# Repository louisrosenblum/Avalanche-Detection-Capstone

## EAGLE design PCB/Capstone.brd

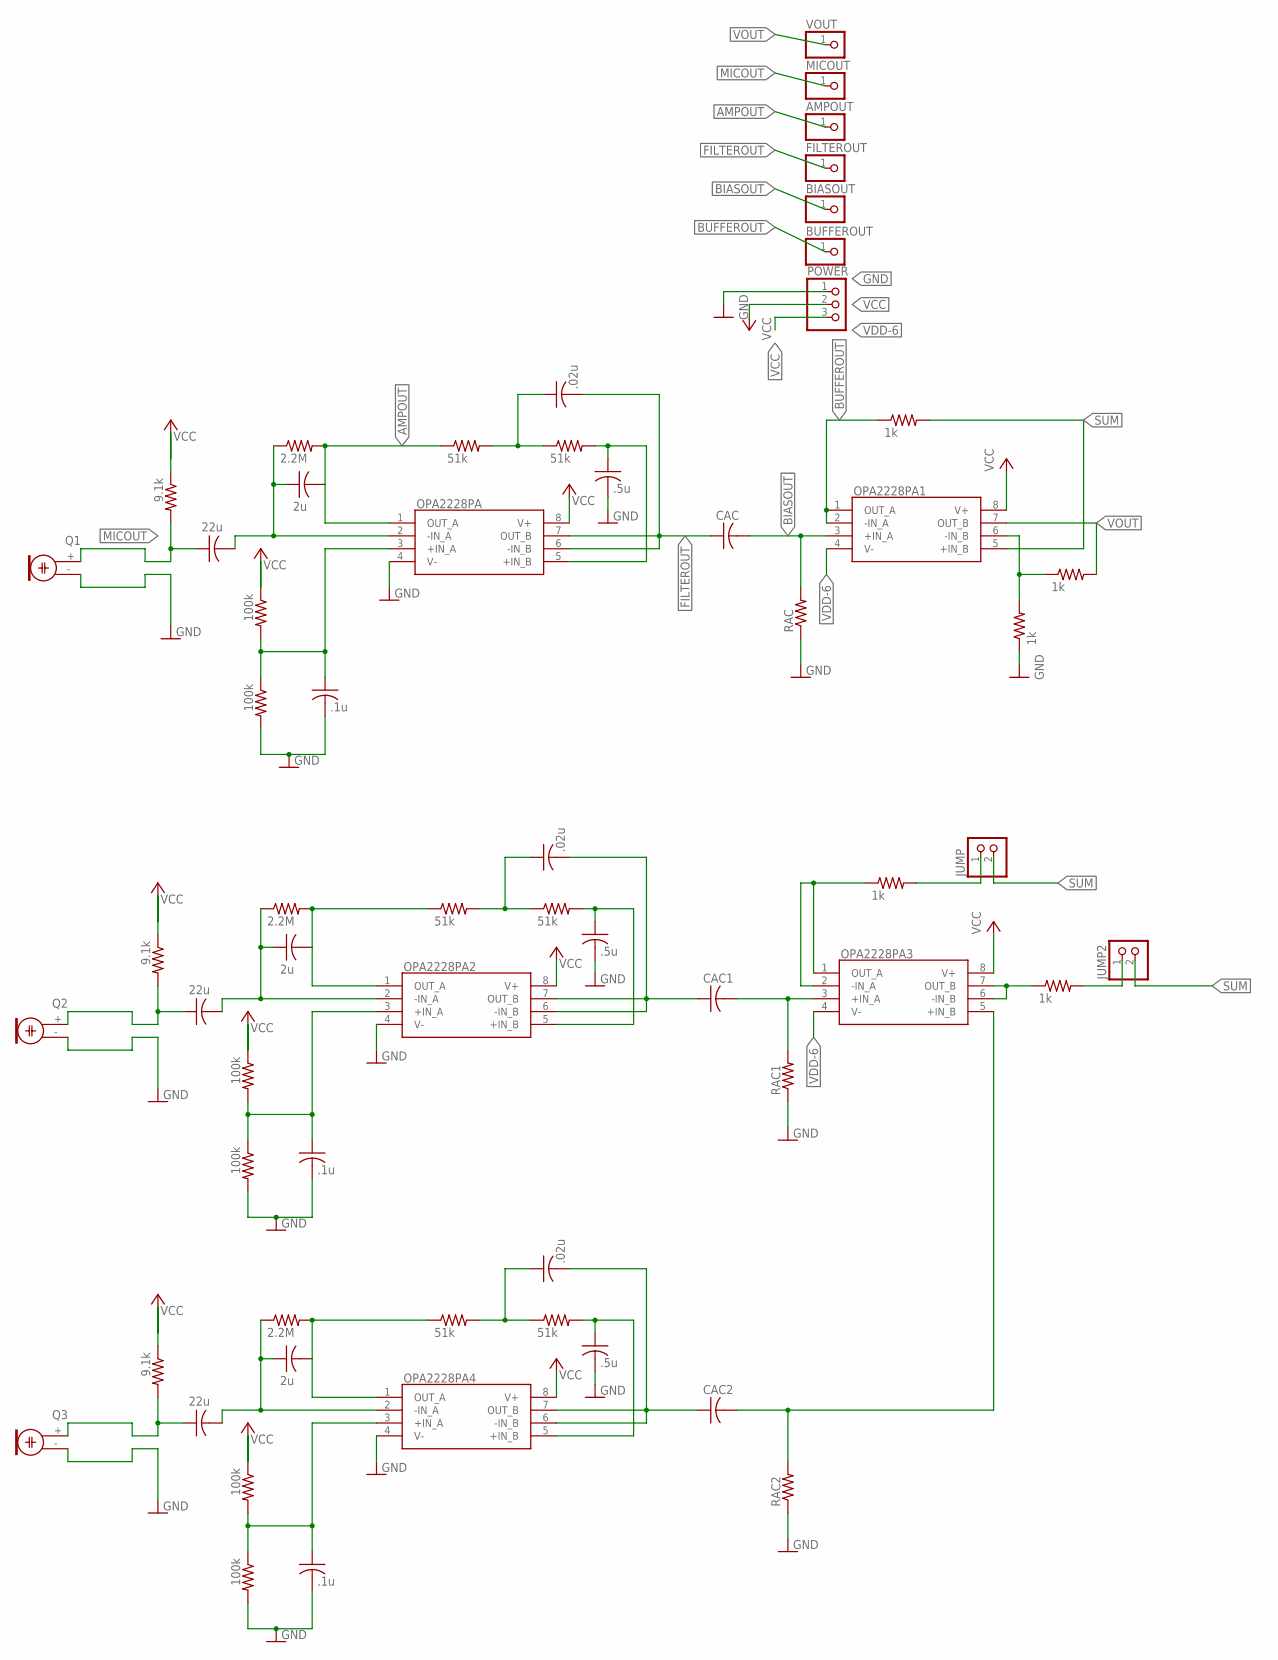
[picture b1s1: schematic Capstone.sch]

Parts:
AMPOUT: PINHD-1X1; 1X01
BIASOUT: PINHD-1X1; 1X01
BUFFEROUT: PINHD-1X1; 1X01
C1, C6, C11: .1u; C025-024X044
C2, C7, C12: 2u; C025-024X044
C3, C8, C13: 22u; C025-024X044
C4, C9, C14: .02u; C025-024X044
C5, C10, C15: .5u; C025-024X044
CAC, CAC1, CAC2: C-US025-024X044; C025-024X044
FILTEROUT: PINHD-1X1; 1X01
JUMP, JUMP2: PINHD-1X2; 1X02
MICOUT: PINHD-1X1; 1X01
OPA2228PA, OPA2228PA1, OPA2228PA2, OPA2228PA3, OPA2228PA4: OPA2228PA; DIP794W53P254L959H508Q8N
POWER: PINHD-1X3; 1X03
Q1, Q2, Q3: ELECTRET; 9.7ELECTRET
R1, R10, R17: 9.1k; 0204/7
R2, R3, R11, R12, R18, R19: 100k; 0204/7
R4, R13, R20: 2.2M; 0204/7
R5, R6, R14, R15, R21, R22: 51k; 0204/7
R7, R8, R9, R16, R23: 1k; 0204/7
RAC, RAC1, RAC2: R-US_0204/7; 0204/7
VOUT: PINHD-1X1; 1X01

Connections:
1: C8.1, Q2.+ (2), R10.2
2: C13.1, Q3.+ (2), R17.2
AMPOUT: AMPOUT.1, C2.2, OPA2228PA.1 (OUT_A), R4.2, R5.1
AMPOUT1: C7.2, OPA2228PA2.1 (OUT_A), R13.2, R14.1
AMPOUT2: C12.2, OPA2228PA4.1 (OUT_A), R20.2, R21.1
BIASOUT: BIASOUT.1, CAC.2, OPA2228PA1.3 (+IN_A), RAC.2
BIASOUT1: CAC1.2, OPA2228PA3.3 (+IN_A), RAC1.2
BIASOUT2: CAC2.2, OPA2228PA3.5 (+IN_B), RAC2.2
BUFFEROUT: BUFFEROUT.1, OPA2228PA1.1 (OUT_A), OPA2228PA1.2 (-IN_A), R8.1
FILTEROUT: C4.2, CAC.1, FILTEROUT.1, OPA2228PA.6 (-IN_B), OPA2228PA.7 (OUT_B)
FILTEROUT1: C9.2, CAC1.1, OPA2228PA2.6 (-IN_B), OPA2228PA2.7 (OUT_B)
FILTEROUT2: C14.2, CAC2.1, OPA2228PA4.6 (-IN_B), OPA2228PA4.7 (OUT_B)
GND: C1.2, C5.2, C6.2, C10.2, C11.2, C15.2, OPA2228PA.4 (V-), OPA2228PA2.4 (V-), OPA2228PA4.4 (V-), POWER.1, Q1.- (1), Q2.- (1), Q3.- (1), R3.2, R7.1, R12.2, R19.2, RAC.1, RAC1.1, RAC2.1
MICOUT: C3.1, MICOUT.1, Q1.+ (2), R1.2
unnamed: C6.1, OPA2228PA2.3 (+IN_A), R11.2, R12.1
unnamed: C2.1, C3.2, OPA2228PA.2 (-IN_A), R4.1
unnamed: OPA2228PA1.6 (-IN_B), R7.2, R9.1
unnamed: C1.1, OPA2228PA.3 (+IN_A), R2.2, R3.1
unnamed: C7.1, C8.2, OPA2228PA2.2 (-IN_A), R13.1
unnamed: C4.1, R5.2, R6.1
unnamed: C5.1, OPA2228PA.5 (+IN_B), R6.2
unnamed: C9.1, R14.2, R15.1
unnamed: JUMP.1, R16.2
unnamed: C10.1, OPA2228PA2.5 (+IN_B), R15.2
unnamed: OPA2228PA3.1 (OUT_A), OPA2228PA3.2 (-IN_A), R16.1
unnamed: C11.1, OPA2228PA4.3 (+IN_A), R18.2, R19.1
unnamed: C12.1, C13.2, OPA2228PA4.2 (-IN_A), R20.1
unnamed: C14.1, R21.2, R22.1
unnamed: C15.1, OPA2228PA4.5 (+IN_B), R22.2
unnamed: OPA2228PA3.6 (-IN_B), OPA2228PA3.7 (OUT_B), R23.1
unnamed: JUMP2.1, R23.2
SUM: JUMP.2, JUMP2.2, OPA2228PA1.5 (+IN_B), R8.2
VCC: OPA2228PA.8 (V+), OPA2228PA1.8 (V+), OPA2228PA2.8 (V+), OPA2228PA3.8 (V+), OPA2228PA4.8 (V+), POWER.2, R1.1, R2.1, R10.1, R11.1, R17.1, R18.1
VDD-6: OPA2228PA1.4 (V-), OPA2228PA3.4 (V-), POWER.3
VOUT: OPA2228PA1.7 (OUT_B), R9.2, VOUT.1

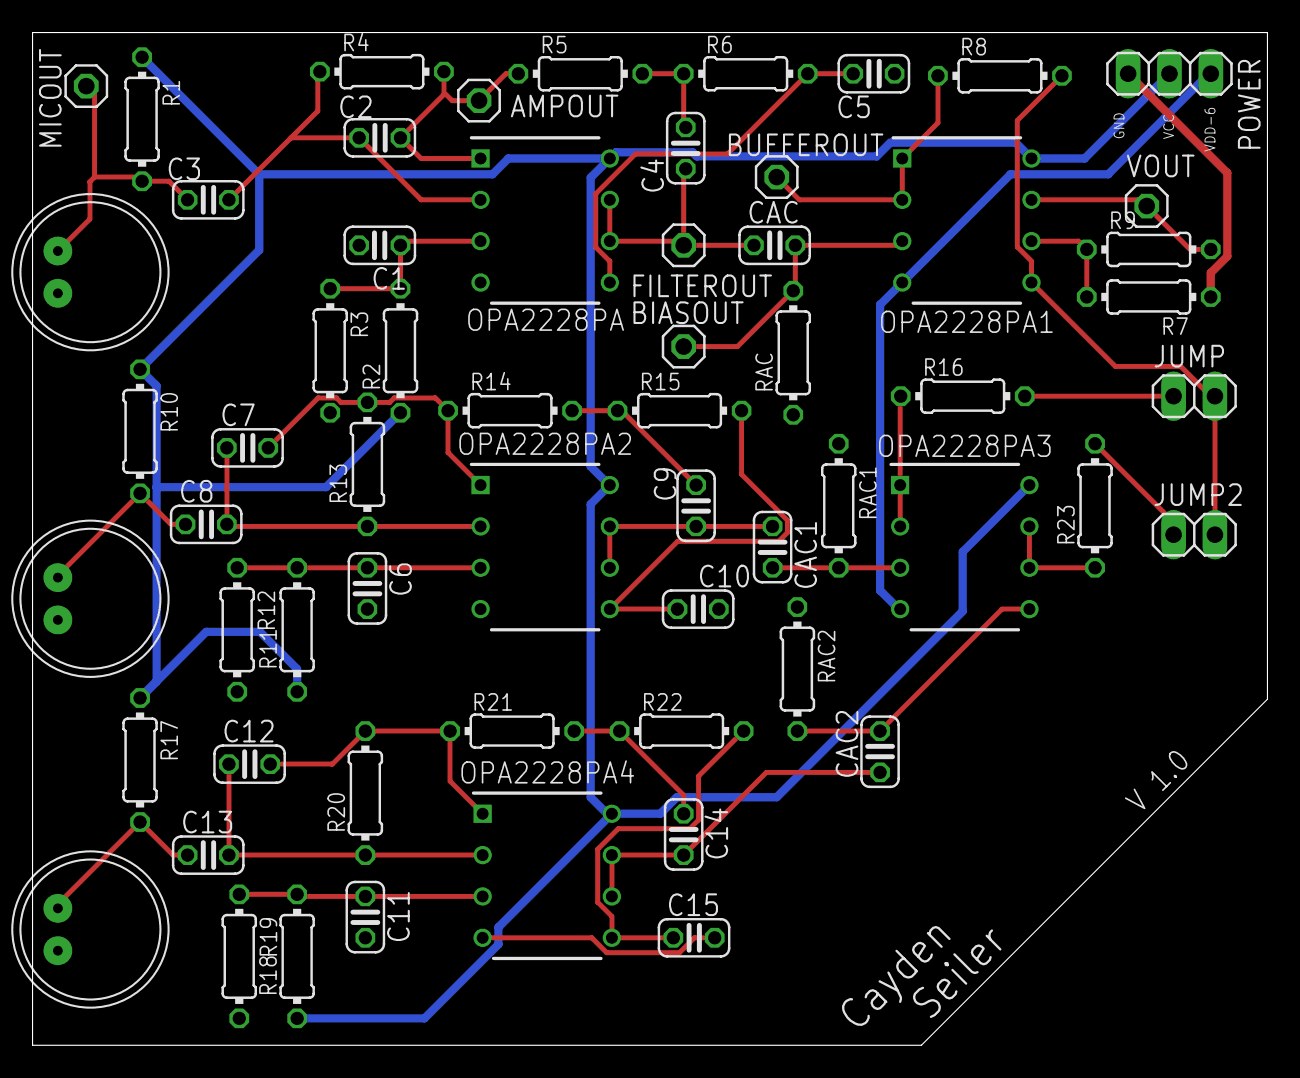
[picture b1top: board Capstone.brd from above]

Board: 2 copper layers, 75.9 x 62.2 mm, 61 parts (0 on the bottom side), 35 nets.

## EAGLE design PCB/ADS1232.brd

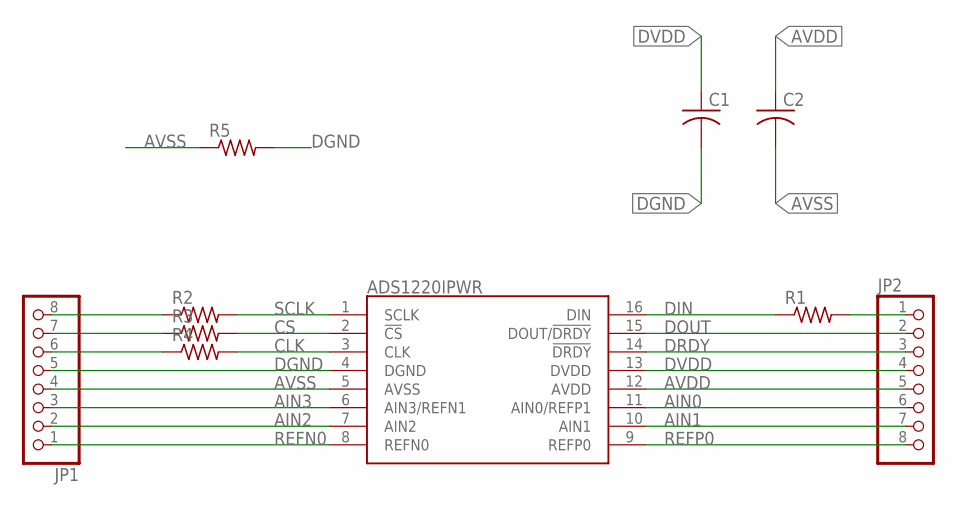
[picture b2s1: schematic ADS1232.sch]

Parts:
C1, C2: C-USC0805K; C0805K
IC1: ADS1220IPWR; SOP65P640X120-16N
JP1, JP2: PINHD-1X8; 1X08
R1, R2, R3, R4, R5: R-US_M2012; M2012

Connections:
AIN0: IC1.11 (AIN0/REFP1), JP2.6
AIN1: IC1.10 (AIN1), JP2.7
AIN2: IC1.7 (AIN2), JP1.2
AIN3: IC1.6 (AIN3/REFN1), JP1.3
AVDD: C2.1, IC1.12 (AVDD), JP2.5
AVSS: C2.2, IC1.5 (AVSS), JP1.4, R5.1
CLK: IC1.3 (CLK), R4.2
CS: IC1.2 (!CS), R3.2
DGND: C1.2, IC1.4 (DGND), JP1.5, R5.2
DIN: IC1.16 (DIN), R1.1
DOUT: IC1.15 (DOUT/!DRDY), JP2.2
DRDY: IC1.14 (!DRDY), JP2.3
DVDD: C1.1, IC1.13 (DVDD), JP2.4
unnamed: JP1.8, R2.1
unnamed: JP1.7, R3.1
unnamed: JP1.6, R4.1
unnamed: JP2.1, R1.2
REFN0: IC1.8 (REFN0), JP1.1
REFP0: IC1.9 (REFP0), JP2.8
SCLK: IC1.1 (SCLK), R2.2

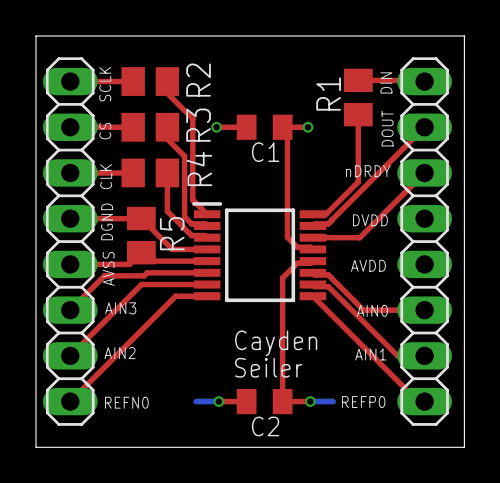
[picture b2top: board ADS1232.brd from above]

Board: 2 copper layers, 23.8 x 22.9 mm, 10 parts (0 on the bottom side), 20 nets.

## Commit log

2019-10-17 Created demo MATLAB file
2019-10-18 Update algorithim_demo.m
    algorithm was spelled incorrectly
2019-10-18 Comment sections
    Added comment sections for each phase of the proposed solution. Subject to change.
2019-10-18 Sensor + Grid intialization
2019-10-19 Added distance function
2019-10-19 Added temperature and dist to sensor calculation
2019-10-22 Revert "Merge branch 'master' of https://github.com/louisrosenblum/Avalanche-Detection-Capstone"
    This reverts commit e92db38a301ff1d19e63b0b130bbb7f123ee42fe, reversing
    changes made to d881027da8f3f1b66a496edd4e60dcea0e339ebe.
2019-10-22 Revert cause i messed up
    Thought I was on my branch and deleted something on accident.
2019-10-22 Finally fixed my mistake....
    Finally fixed my mistake from the previous commits. I believe these are the most current ones Louis from when you worked on it.
2019-10-22 Added automatic plot of layout
2019-10-23 New Temp Formula
    New temp formula and fixed the creation of the grid matrix.
2019-10-23 Fixed errors
2019-10-24 Added true origin to plot
2019-10-24 test
2019-10-24 Added part of the noise addition
    Added noise to a .wav file that we can use for the
2019-10-26 Added signal generation
2019-10-26 Coded geolocation algorithim, added gaussian noise to signals
2019-10-26 Fixed script output
2019-11-04 Added plot labels
    Added plot labels for signal plot and grid plot
2019-11-04 Multiple Simulations
    Created script.m to run the simulation multiple times with unfiltered and filtered input signals to find the average percent error. All lines are suppressed except for percent error to clean up .txt 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
2019-11-05 Re-added beamform plot
2019-11-05 Fixed script variable output
2019-11-05 Re-added low-pass filters to algorithim execution
2019-11-05 Added avalanche detection print statement and additional comments
2019-11-05 Added additional comments
2019-11-05 Changed threshold from 90% to 80%
2019-11-06 Updated sampling rate
2019-11-07 Added probability determination and unfiltered beamform plot
2019-11-07 Added probability of correct origin prediction
2019-11-07 stuff
2019-11-08 Fixed algorithim method
2019-11-11 Signal detection at 10hz
2019-11-11 Used fft to detect 10hz frq
2019-11-11 Added comments and verified detection frequency
2019-11-11 Created version with amplitude decay, using snr for geolocation
2019-11-12 Changed decay algorithim from snr to non-boosted amplitude
2019-11-12 added
2019-11-12 Removed filters, added labels
2019-11-12 SNR range, Changed Algorithim to Algorithm
    Changed SNR range to 30 instead of 100. Also suppressed some outputs and deleted outdated commented out code.
2019-11-13 Added plots to a subplot
    Instead of having three seperate plots we now have one figure split into three subplots.
2019-11-13 Renamed avalanche to signal
2019-11-13 Added histogram.m
2019-11-13 Added histogram generation to script
2019-11-14 Fixed histogram comparison parameter
2019-11-14 Added more comments, moved some versions to old versions folder
2019-11-14 Updated date
2019-11-14 Renamed some labels
2019-11-14 hist
2019-11-14 Added noise test
2019-11-14 Added prob prints
2019-11-14 Added test noise to plot
2019-11-14 Renamed z-score variable
2019-11-14 Changed some comments
2019-11-15 Moved into demo script folder
2020-01-18 Forked main for 3D development
2020-01-18 Added sensor elevations by hand
2020-01-24 Added heatmap to script
2020-01-24 Heatmap Update
2020-01-25 Changed signal from sin to sinc
2020-01-25 Renamed directories
2020-01-25 Renamed image file
2020-01-26 Took additional screenshots
2020-01-28 Added random waveform
2020-01-31 Added error calculation
2020-01-31 Added logbase function
2020-01-31 Fixed syntax error
2020-02-01 Updated heatmap
2020-02-05 Updated plot labels
2020-02-08 Added error circle
2020-02-13 Finished error updates
2020-02-14 Added screenshots
2020-02-20 Intersecting directions draft
2020-02-20 Updated new 3D simulation
2020-02-20 Updated heatmap scale factor
2020-02-21 Re-added error calculation
2020-02-21 Added BeamFormer SimuLink component
2020-02-23 Added sensor permutation, lowered elevation resolution
2020-02-23 Diary Script for Averaging
    Added diary script for averaging. Best used if all outputs are suppressed except for the one in question
2020-02-24 Began optimization study
2020-02-24 Added Example SimuLink Model for design reference
2020-02-25 Additional optimization study
2020-02-28 Updated beamformer simulink model
2020-02-28 Finished optimization study
2020-02-28 Reverted changes
2020-03-02 Created version 1.6
2020-03-02 Updated threshold comparisons
2020-03-05 Added confidence threshold
2020-03-06 Updated SimuLink model to use dual port ram for roating buffer
2020-03-06 Fixed print statements
2020-03-06 Modified simulink model
2020-03-06 Added Simulink test bench
2020-03-07 Added multiple RAM components to SimuLink model
2020-03-10 Fixed fft
2020-03-11 Added report figures
2020-03-20 PCB
    Added PCB files used to make final board and a new ADC board
2020-04-04 Updated number of sensors buffers
2020-04-13 Added init function for Simulink model
2020-04-13 Updated simulink model
    Added uint16 signal conditioning path, upgraded RAM size
2020-05-01 Added all spring 2020 resources
2020-05-04 -added some edits to simulink model and testbench
2020-05-04 addded beamformer final
